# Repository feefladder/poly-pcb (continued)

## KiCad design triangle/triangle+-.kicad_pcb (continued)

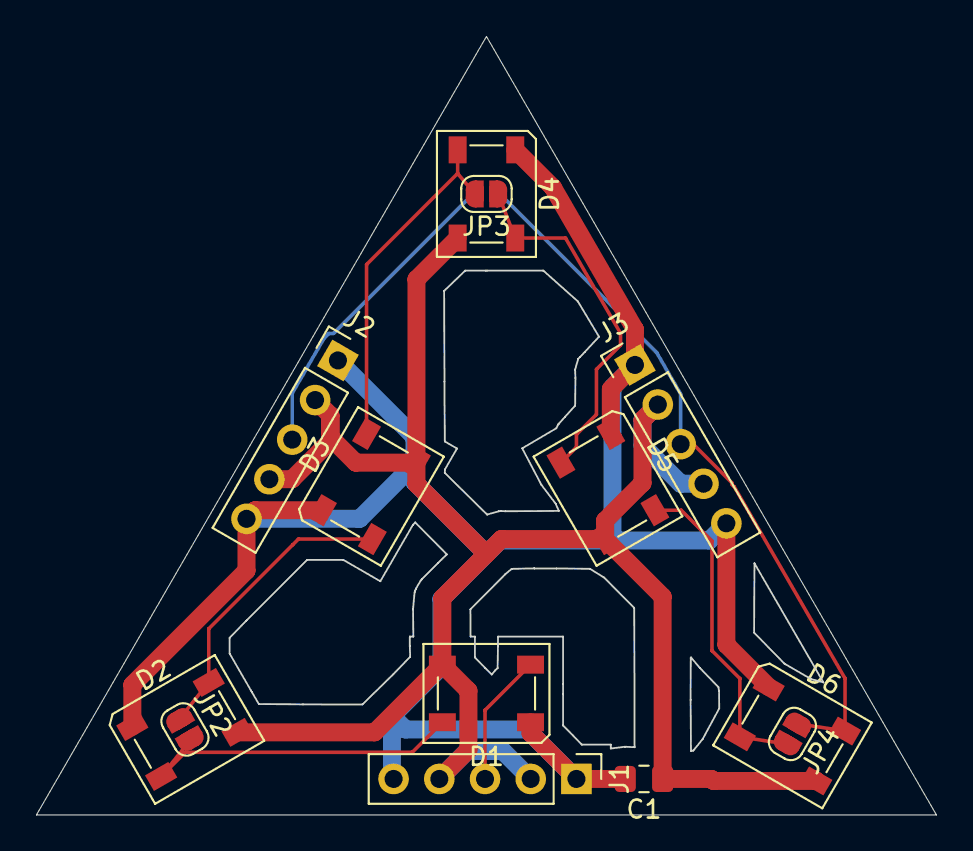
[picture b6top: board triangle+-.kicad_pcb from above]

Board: 2 copper layers, 50.0 x 43.2 mm, 14 parts (1 on the bottom side), 10 nets.

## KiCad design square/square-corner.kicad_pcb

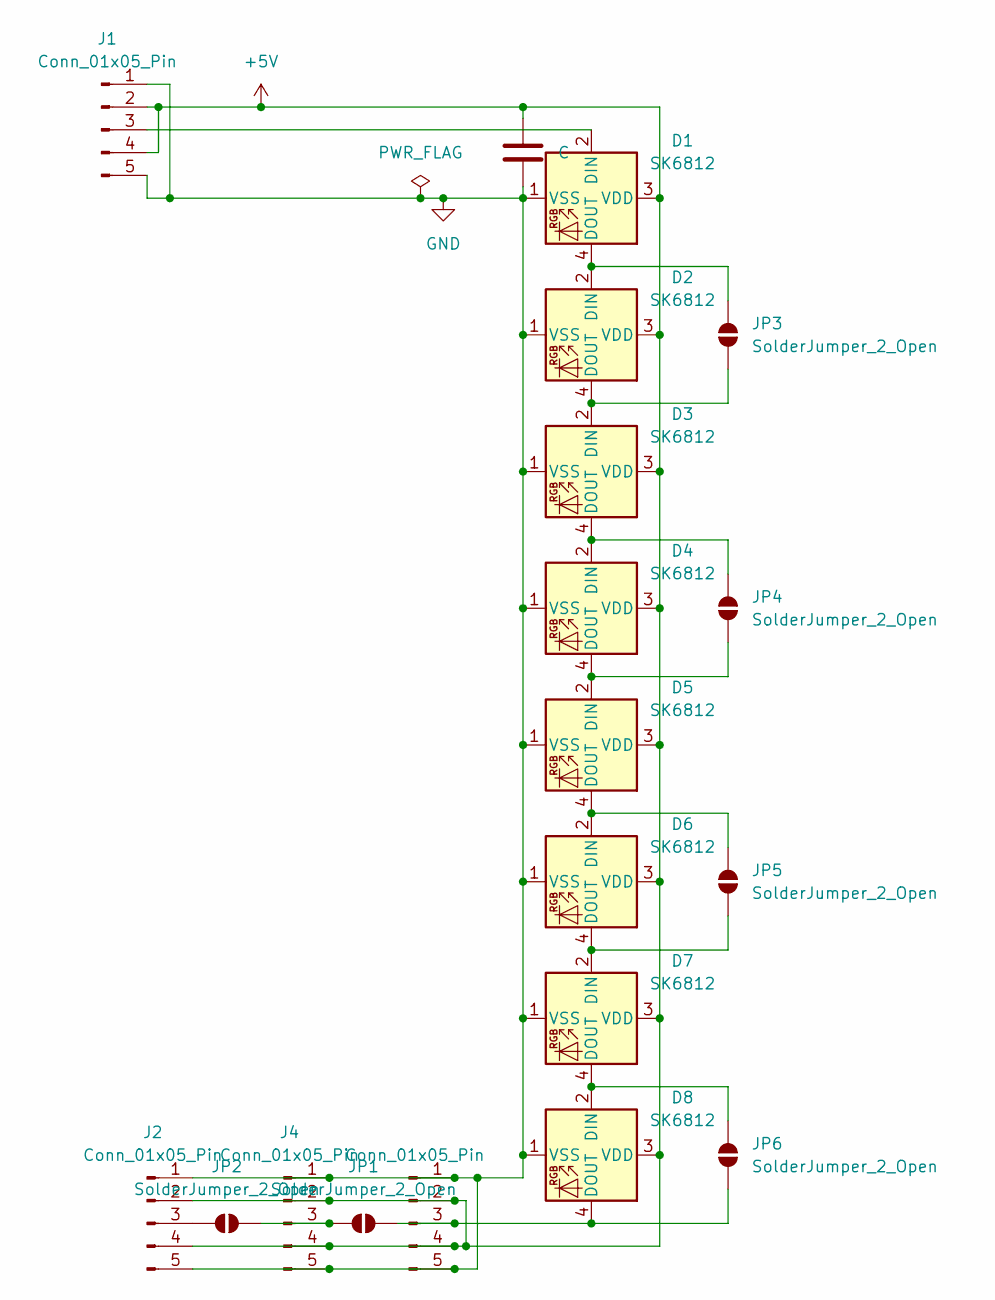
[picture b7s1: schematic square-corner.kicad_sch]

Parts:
C1: C; C_0805_2012Metric_Pad1.18x1.45mm_HandSolder
D1, D2, D3, D4, D5, D6, D7, D8: SK6812; LED_SK6812_PLCC4_5.0x5.0mm_P3.2mm
J1, J2, J3, J4: Conn_01x05_Pin; PinHeader_1x05_P2.54mm_Vertical
JP1, JP2: SolderJumper_2_Open; SolderJumper-2_P1.3mm_Open_Pad1.0x1.5mm
JP3, JP4, JP5, JP6: SolderJumper_2_Open; SolderJumper-2_P1.3mm_Open_RoundedPad1.0x1.5mm

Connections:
+5V: C1.2, D1.3 (VDD), D2.3 (VDD), D3.3 (VDD), D4.3 (VDD), D5.3 (VDD), D6.3 (VDD), D7.3 (VDD), D8.3 (VDD), J1.2, J1.4, J2.2, J2.4, J3.2, J3.4, J4.2, J4.4
GND: C1.1, D1.1 (VSS), D2.1 (VSS), D3.1 (VSS), D4.1 (VSS), D5.1 (VSS), D6.1 (VSS), D7.1 (VSS), D8.1 (VSS), J1.1, J1.5, J2.1, J2.5, J3.1, J3.5, J4.1, J4.5
unnamed: D1.2 (DIN), J1.3
unnamed: D1.4 (DOUT), D2.2 (DIN), JP3.2 (B)
unnamed: D2.4 (DOUT), D3.2 (DIN), JP3.1 (A)
unnamed: D3.4 (DOUT), D4.2 (DIN), JP4.2 (B)
unnamed: D4.4 (DOUT), D5.2 (DIN), JP4.1 (A)
unnamed: D5.4 (DOUT), D6.2 (DIN), JP5.2 (B)
unnamed: D6.4 (DOUT), D7.2 (DIN), JP5.1 (A)
unnamed: D7.4 (DOUT), D8.2 (DIN), JP6.2 (B)
unnamed: D8.4 (DOUT), J3.3, JP1.2 (B), JP6.1 (A)
unnamed: J2.3, JP2.1 (A)
unnamed: J4.3, JP1.1 (A), JP2.2 (B)

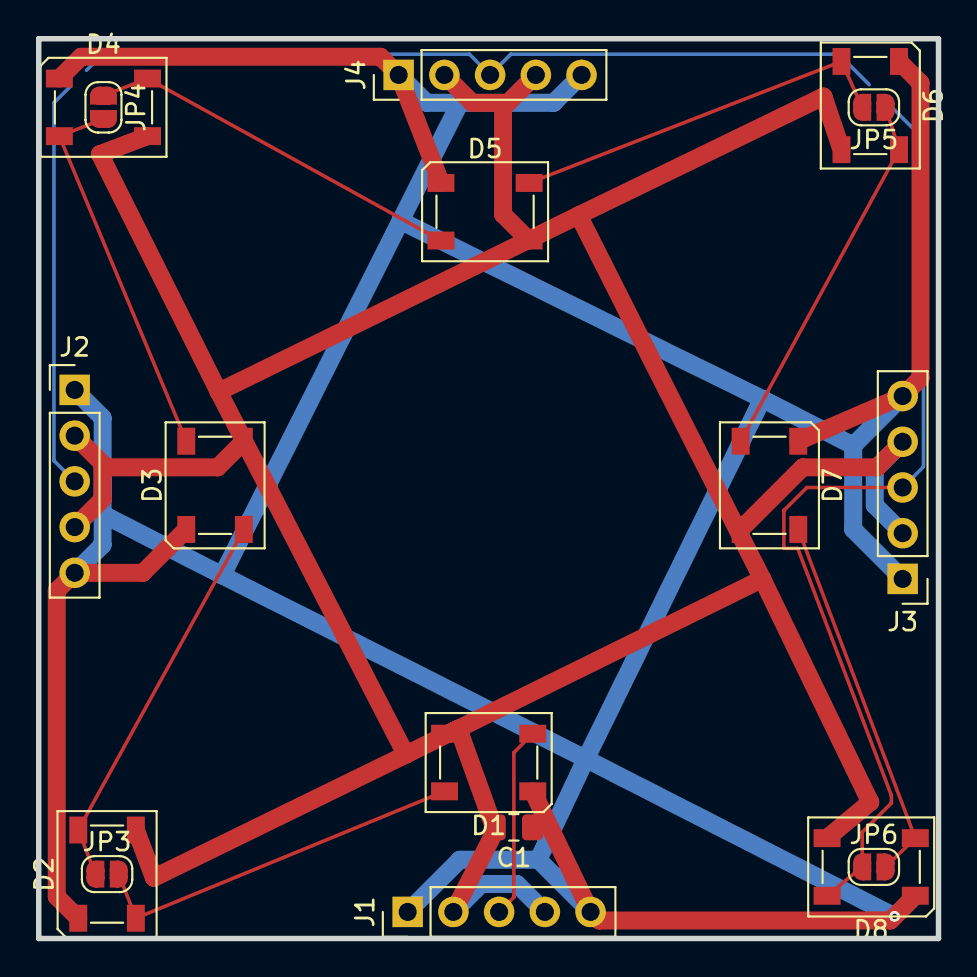
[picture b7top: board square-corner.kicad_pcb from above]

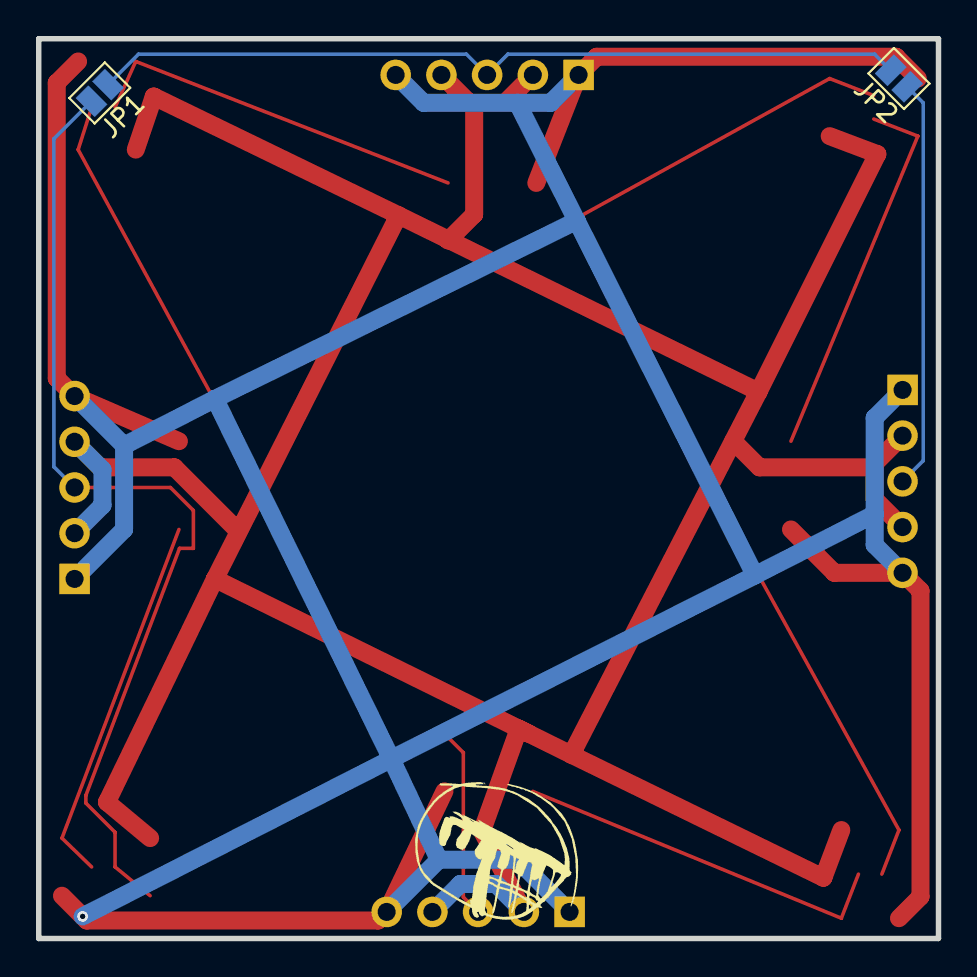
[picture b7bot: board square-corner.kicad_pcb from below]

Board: 2 copper layers, 50.0 x 50.0 mm, 19 parts (2 on the bottom side), 13 nets.

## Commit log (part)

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2026-05-07 great success!
2026-06-01 updated all coolness
2026-06-10 added mic to antenna, decagons, octagons and all the shenanigans
2026-06-23 hello rusqlite-wasm
2026-06-25 fixed BQ24040DSQR layout to be 2x2mm in stead of 2.5, also added heat pad after actually reading datasheet lol
2026-06-25 fixed unconnected jumper wire
2026-06-25 I have no idea what I did
2026-06-25 improved stand, magnateddy impression
2026-06-25 UGLY SPINNING CUBEgit add ..1!
2026-06-25 spaghetti, will start from example
2026-06-27 polygon switching working!
2026-06-27 ugly resizing of screen every frame to fix huge pixels bc of not resizing at events or start
2026-06-27 per-face instancing and stl loading working, need put together
2026-06-27 ci: initial workflow for pages
2026-06-28 triangle pcbs now on faces, still offset somehow
2026-06-28 deploy: 766b981d3721374080ecc55992a54951db2527f4
2026-06-28 deploy: f5e54d2b2934bc4b06ff3e1095cb6f9b10c63600
2026-06-28 deploy: f2ab9b5716caa950fdb4d96648eae13a5cc02b75
2026-06-28 deploy: 4ef51fe17938dee02f9c097b01387d2769c947dd
2026-06-28 deploy: 6b8be604a0cd3b393e8de0d1637acf060b71bfca
2026-06-28 it works!
2026-06-28 deploy: 526bd5ab184792b4d241cf8dd182f6c643c67e96
2026-06-28 add stl files
2026-06-28 added logging
2026-06-28 deploy: 20261f785b1372180862fe8cacc27af4f497a32f
2026-06-28 deploy: 49027d5ba170593fc42cee515820bcd03e4cf263
2026-06-28 fixed wrong offsets
2026-06-28 deploy: f9bb231a502a2ae18162dc9bf4ce131a682bfaf6
2026-06-28 some renaming, shifted triangle and pentagon to fit
2026-06-28 deploy: ede23deabf14775c8945f7e1598eec2647007432
2026-06-28 space/tab cycling (with event hook js-side) and raycasting on mouse click
2026-06-28 deploy: 505e6b5ba0238fc792b74abd5e0001dcfa7cef45
2026-06-28 fixed resizing behaviour, added 8- and 10-gon stls
2026-06-28 deploy: 1d6ca06d52dfcaa9cc60bac14ba280cb0edf4080
2026-06-28 convert stl to binary
2026-06-28 deploy: 7338c0bc50ac74772f4c39c77990c93de844849b
2026-06-29 mouse ui
2026-06-29 fix workflow, remove warnings
2026-06-29 deploy: c3fe9999f2ff95b305a85279fdf6d1a93c838a74
2026-06-29 WIP: face clicky, before ui.rs
2026-06-29 refactor: move ui stuff to ui.rs
2026-06-29 change face works buggily
2026-06-29 deploy: 82fdf83d4c8d6f6ba28d44150dcc3146c623f0fb
2026-06-29 fixed pointing issue, was flipped y in physical pixel calculation
2026-06-29 deploy: 3dc40e5831e33ed0069c04a1f205b7627593c451
2026-06-29 removed noisy debug message
2026-06-29 deploy: b8ec533f2f27b101c6edf4d12bea078d5bc51cce
2026-06-30 no more re-uploading meshes to GPU! plumbing for variant inputs
2026-06-30 deploy: b9b27f389822dfd2142f505dd1bccdbd94f47b35
2026-06-30 url-update and some bla
2026-06-30 deploy: b26d0704af563fd545c55cfef2a256714186509c
